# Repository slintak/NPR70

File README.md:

# NPR70 — New Packet Radio for 70 cm Band

A complete open-source hardware and firmware project for a modern IP packet
radio modem operating on the 70 cm amateur band (420–450 MHz).  Compatible with
the NPR [New Packet Radio](https://hackaday.io/project/164092-npr-new-packet-radio),
but with custom hardware and improvements for easier DIY assembly.

## What is NPR70?

**NPR70** is an open-source implementation of a New Packet Radio (NPR) modem — a
  protocol and hardware design for transmitting IP packets over UHF (70 cm)
  amateur radio, with the following goals:

- High throughput (typically 50–500 kbps gross rate)
- Reliable point-to-multipoint IP networking (TCP/IP, UDP, etc.)
- Fully open hardware and software
- Minimal latency and straightforward configuration

This project is **primarily for amateur radio operators** interested in building
and experimenting with modern digital data networks, Hamnet, telemetry, or
similar applications on the UHF band.

It is a fork/derivative of the
[original NPR project by F4HDK](https://hackaday.io/project/164092-npr-new-packet-radio),
but with new custom hardware, simplified design, and refactored/cleaned firmware.

## Who is this for?

- Licensed amateur radio operators interested in high-speed IP digital modes
- Hamnet and HSMM enthusiasts
- Anyone interested in open hardware wireless networking on UHF

## Hardware Overview

- **MCU**: STM32 microcontroller (STM32L432KCU, as in original)
- **RF Module**: NiceRF module for 70 cm UHF band  (based on SI4463)
- **Ethernet**: W5500 (SPI, 10/100 Mbps Ethernet controller)
- **Form Factor**: Two layer 69×100 mm PCB
- **Other**: 0402 SMD passives, SMA, Ethernet and USB-C connectors, etc.

The hardware is designed to be compact and affordable, with a focus on
DIY manufacturing and community development. All schematics and layout
files are in the [`pcb/`](pcb/) directory.

## Firmware Details

- Based on **MbedOS 5.6.6** (last version compatible with the original code)
- Derived from the [F4HDK NPR firmware]
  (https://github.com/f4hdk/NewPacketRadio), but refactored and cleaned up for
  different pinout
- Supports all main NPR features (TDMA master/slave, 2GFSK/4GFSK,
  point-to-multipoint IP bridging)
- Compatible with official NPR protocol and other compatible modems

## Key Features

| Feature        | Details                                                     |
|----------------|-------------------------------------------------------------|
| **Protocol**   | NPR (custom IP radio, NOT AX.25; true L3)                   |
| **Topology**   | Point-to-multipoint (master + up to 7 clients), TDMA        |
| **Modulation** | 2GFSK / 4GFSK, up to 500 kbps gross (see protocol docs)     |
| **RF Band**    | 70 cm amateur band (configurable, typically 430–440 MHz)    |
| **Network**    | Full IP stack, transparent bridging, works with DHCP, TCP/IP, UDP, etc. |
| **Range**      | Up to 300 km line-of-sight (with suitable antennas and power) |
| **Hardware**   | STM32 MCU, SI4463 radio, W5500 Ethernet, all open hardware  |
| **License**    | GPL v3.0 (same as original NPR project)                     |

## Repository Structure

- `pcb/` – KiCAD project directory (schematic and PCB layout).
- `src/` – Firmware source code, based on MbedOS (legacy version), derived and
  adapted from the original NPR project.

## Quick Start

1. **Hardware**: Manufacture or assemble the PCB found in `pcb/`. BOM and
   assembly notes are included.
2. **Firmware**:
    - For building the code by youself, you will need Debian based system and
      installed `gcc-arm-none-eabi`.
    - Build firmware by running `make` in the `src/` directory.
    - Firmware binary is in  the `src/BUILD/NPR70.hex` file
    - Flash firmware to the STM32 MCU using an SWD programmer
      `pyocd load -t stm32l432kc BUILD/NPR70.hex`
3. **Configuration**: Adjust radio parameters (frequency, bandwidth,
   master/client mode, IP addresses) as described in the
   [original NPR documentation](https://cdn.hackaday.io/files/1640927020512128/NPR70_introduction_EN_v3.6.pdf)
4. **Connect**: Plug in Ethernet and power, connect antenna, and start experimenting

Basic settings to check (more details in the original NPR documentation):

* `display config`: show current configuration
* `set <param> <value>`: store value to the given parameter
* `save`: saves current configuration into the EEPROM
* `radio on`/`radio off`: turn RF on or off
* `reboot`: reboot the FW

You have to set your callsign, frequency and modulation. Rest of the parameters
is up to you and your setup.

```
set callsign AB1CDE
set frequency 434.200
set modulation 22
```

## Documentation and References

- [Original NPR project by F4HDK](https://hackaday.io/project/164092-npr-new-packet-radio)
- [Official NPR documentation (PDFs, guides, protocol)](https://cdn.hackaday.io/files/1640927020512128/NPR70_introduction_EN_v3.6.pdf)
- [Project homepage and build log (in Czech)](https://uart.cz/2773/the-new-packet-radio/)

## License

This project is released under the **GPL v3.0 license**, same as the original
NPR project by F4HDK. See [LICENSE](LICENSE) for full details.

## Contributing

Contributions are welcome! You can:

- Submit hardware design improvements (new PCB revisions, bugfixes)
- Help with firmware optimization, porting to newer MbedOS versions, or adding
  features
- Share test results, deployment reports, and real-world feedback
- Translate documentation

For major changes, please open an issue first to discuss what you would like to
change.

If you have questions or suggestions, feel free to open an
[issue](https://github.com/slintak/NPR70/issues).

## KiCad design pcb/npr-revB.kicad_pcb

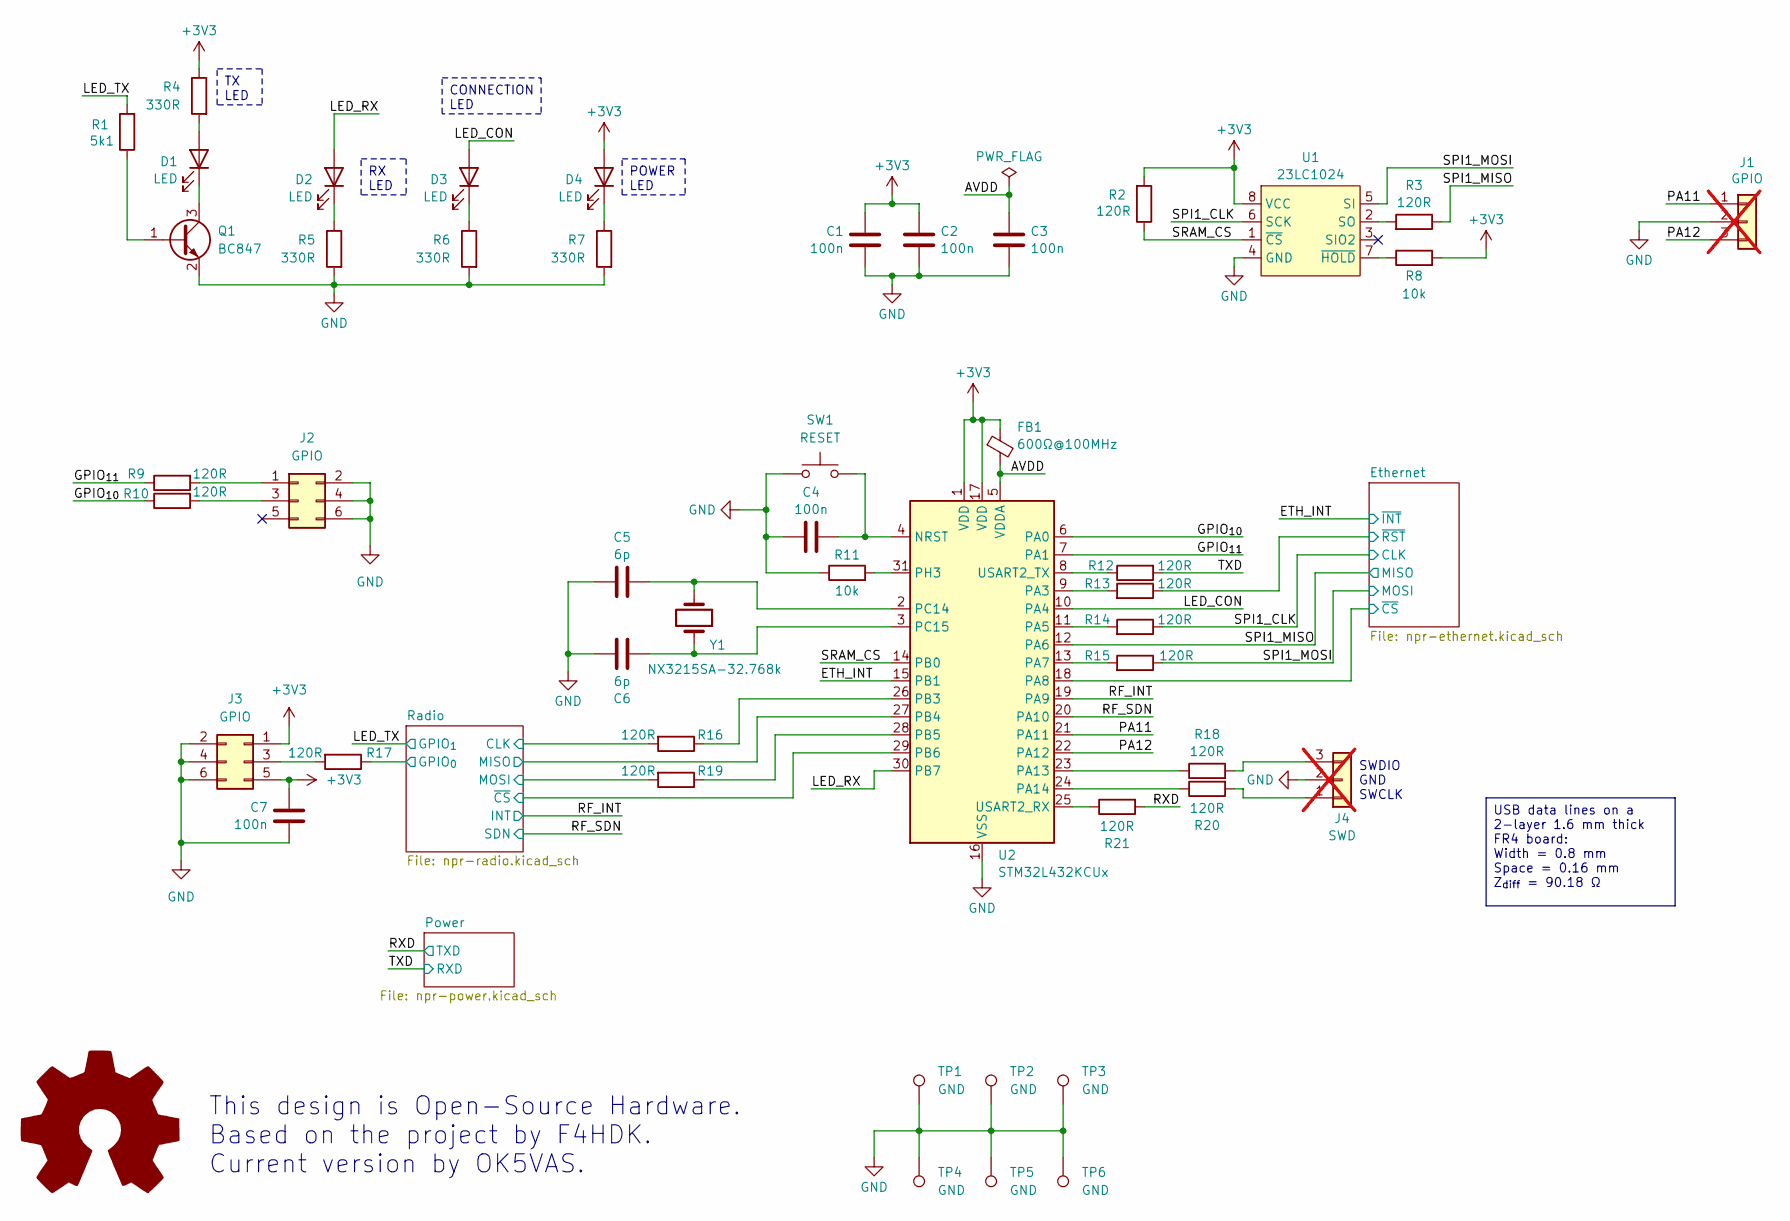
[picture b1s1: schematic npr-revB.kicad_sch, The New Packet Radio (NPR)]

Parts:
C1, C2, C3, C4, C7: 100n; C_0402_1005Metric; LCSC C1525
C5, C6: 6p; C_0402_1005Metric; LCSC C700515
D1, D2, D3, D4: LED; LED_0603_1608Metric; LCSC C2286
FB1: 600Ω@100MHz; L_0603_1608Metric; LCSC C19330
J1: GPIO; PinHeader_1x03_P2.54mm_Vertical; not fitted
J2, J3: GPIO; IDC-Header_2x03_P2.54mm_Horizontal; LCSC C34945
J4: SWD; PinHeader_1x03_P2.54mm_Vertical; not fitted
Q1: BC847; SOT-23; LCSC C57668
R1: 5k1; R_0402_1005Metric; LCSC C25905
R2, R3, R9, R10, R12, R13, R14, R15, R16, R17, R18, R19, R20, R21: 120R; R_0402_1005Metric; LCSC C25079
R4, R5, R6, R7: 330R; R_0402_1005Metric; LCSC C12246
R8, R11: 10k; R_0402_1005Metric; LCSC C25744
SW1: RESET; SW_SPST_CK_RS282G05A3; LCSC C483808
TP1, TP2, TP3, TP4, TP5, TP6: GND; TestPoint_Pad_D3.0mm
U1: 23LC1024; SOP-8_3.9x4.9mm_P1.27mm; LCSC C48388
U2: STM32L432KCUx; QFN-32-1EP_5x5mm_P0.5mm_EP3.45x3.45mm; LCSC C1337280
Y1: NX3215SA-32.768k; Crystal_SMD_3215-2Pin_3.2x1.5mm; LCSC C156244

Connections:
+3V3: C1.1, C2.1, C7.1, D4.2 (A), FB1.1, J3.1, J3.5, R2.2, R4.1, R8.2, U1.8 (VCC), U2.1 (VDD), U2.17 (VDD); also elsewhere on the board
/AVDD: C3.1, FB1.2, U2.5 (VDDA)
/ETH_INT: U2.15 (PB1); also elsewhere on the board
/Ethernet/~CS: U2.18 (PA8); also elsewhere on the board
/Ethernet/~RST: R13.1; also elsewhere on the board
/GPIO_{10}: R10.1, U2.6 (PA0)
/GPIO_{11}: R9.1, U2.7 (PA1)
/LED_CON: D3.2 (A), U2.10 (PA4)
/LED_RX: D2.2 (A), U2.30 (PB7)
/LED_TX: R1.2; also elsewhere on the board
/PA11: J1.1, U2.21 (PA11)
/PA12: J1.3, U2.22 (PA12)
/RF_INT: U2.19 (PA9); also elsewhere on the board
/RF_SDN: U2.20 (PA10); also elsewhere on the board
/RXD: R21.2; also elsewhere on the board
/Radio/CLK: R16.2; also elsewhere on the board
/Radio/GPIO_{0}: R17.1; also elsewhere on the board
/Radio/MISO: U2.27 (PB4); also elsewhere on the board
/Radio/MOSI: R19.2; also elsewhere on the board
/Radio/~CS: U2.29 (PB6); also elsewhere on the board
/SPI1_CLK: R14.1, U1.6 (SCK); also elsewhere on the board
/SPI1_MISO: R3.1, U2.12 (PA6); also elsewhere on the board
/SPI1_MOSI: R15.1, U1.5 (SI); also elsewhere on the board
/SRAM_CS: R2.1, U1.1 (~CS), U2.14 (PB0)
/TXD: R12.2; also elsewhere on the board
GND: C1.2, C2.2, C3.2, C4.1, C5.1, C6.1, C7.2, J1.2, J2.2, J2.4, J2.6, J3.2, J3.4, J3.6, J4.2, Q1.2 (E), R5.2, R6.2, R7.2, R11.1, SW1.1, TP1.1, TP2.1, TP3.1, TP4.1, TP5.1, TP6.1, U1.4 (GND), U2.16 (VSS), U2.32 (VSS), U2.33 (VSS); also elsewhere on the board
unnamed: D1.2 (A), R4.2
unnamed: D1.1 (K), Q1.3 (C)
unnamed: D2.1 (K), R5.1
unnamed: D3.1 (K), R6.1
unnamed: D4.1 (K), R7.1
unnamed: J2.1, R9.2
unnamed: J2.3, R10.2
unnamed: J3.3, R17.2
unnamed: J4.1, R20.2
unnamed: J4.3, R18.2
unnamed: Q1.1 (B), R1.1
unnamed: R3.2, U1.2 (SO)
unnamed: R8.1, U1.7 (~HOLD)
unnamed: C4.2, SW1.2, U2.4 (NRST)
unnamed: R12.1, U2.8 (USART2_TX)
unnamed: R13.2, U2.9 (PA3)
unnamed: R14.2, U2.11 (PA5)
unnamed: R15.2, U2.13 (PA7)
unnamed: R18.1, U2.23 (PA13)
unnamed: R20.1, U2.24 (PA14)
unnamed: R21.1, U2.25 (USART2_RX)
unnamed: R16.1, U2.26 (PB3)
unnamed: R19.1, U2.28 (PB5)
unnamed: C5.2, U2.2 (PC14), Y1.2
unnamed: C6.2, U2.3 (PC15), Y1.1
unnamed: R11.2, U2.31 (PH3)

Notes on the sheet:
This design is Open-Source Hardware. Based on the project by F4HDK. Current version by OK5VAS.
SWDIO GND SWCLK
RX LED
CONNECTION LED
TX LED
POWER LED
USB data lines on a 2-layer 1.6 mm thick FR4 board: Width = 0.8 mm Space = 0.16 mm Z_{diff} = 90.18 Ω

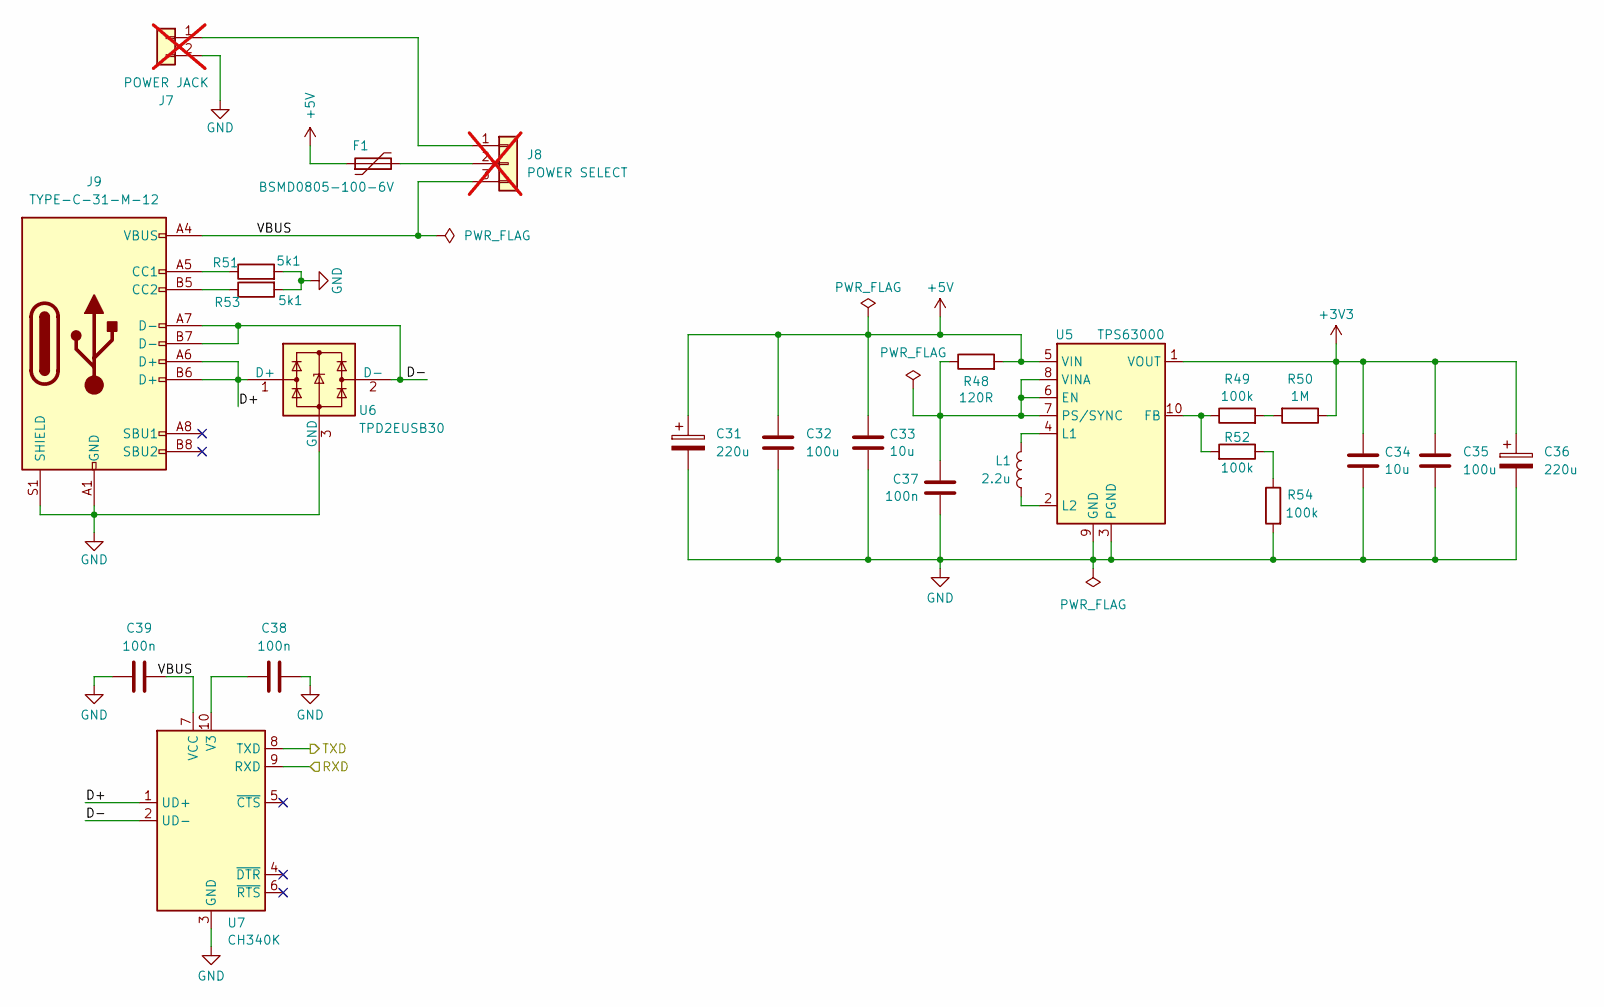
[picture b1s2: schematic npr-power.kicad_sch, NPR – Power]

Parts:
C31, C36: 220u; CP_Elec_6.3x5.4; LCSC C2833309
C32, C35: 100u; C_1206_3216Metric; LCSC C15008
C33, C34: 10u; C_0603_1608Metric; LCSC C19702
C37, C38, C39: 100n; C_0402_1005Metric; LCSC C1525
F1: BSMD0805-100-6V; Fuse_0805_2012Metric; LCSC C883112
J7: POWER JACK; PinHeader_1x02_P2.54mm_Vertical; not fitted
J8: POWER SELECT; PinHeader_1x03_P2.54mm_Vertical; not fitted
J9: TYPE-C-31-M-12; USB_C_Receptacle_HRO_TYPE-C-31-M-12; LCSC C165948
L1: 2.2u; L_Taiyo-Yuden_MD-3030; LCSC C5159665
R48: 120R; R_0402_1005Metric; LCSC C25079
R49, R52, R54: 100k; R_0402_1005Metric; LCSC C25741
R50: 1M; R_0402_1005Metric; LCSC C26083
R51, R53: 5k1; R_0402_1005Metric; LCSC C25905
U5: TPS63000; Texas_DRC0010J_ThermalVias; LCSC C24966
U6: TPD2EUSB30; Texas_DRT-3; LCSC C97502
U7: CH340K; SSOP-10-1EP_3.9x4.9mm_P1mm_EP2.1x3.3mm; LCSC C18208922

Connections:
+3V3: C34.1, C35.1, C36.1, R50.1, U5.1 (VOUT); also elsewhere on the board
+5V: C31.1, C32.1, C33.1, F1.1, R48.2, U5.5 (VIN); also elsewhere on the board
/Power/D+: J9.A6 (D+), J9.B6 (D+), U6.1 (D+), U7.1 (UD+)
/Power/D-: J9.A7 (D-), J9.B7 (D-), U6.2 (D-), U7.2 (UD-)
/Power/VBUS: C39.2, J8.3, J9.A4 (VBUS), J9.A9 (VBUS), J9.B4 (VBUS), J9.B9 (VBUS), U7.7 (VCC)
/RXD: U7.8 (TXD); also elsewhere on the board
/TXD: U7.9 (RXD); also elsewhere on the board
GND: C31.2, C32.2, C33.2, C34.2, C35.2, C36.2, C37.2, C38.2, C39.1, J7.2, J9.A1 (GND), J9.A12 (GND), J9.B1 (GND), J9.B12 (GND), J9.S1 (SHIELD), R51.2, R53.2, R54.2, U5.3 (PGND), U5.9 (GND), U5.11 (PGND), U6.3 (GND), U7.3 (GND), U7.11 (GND); also elsewhere on the board
unnamed: J7.1, J8.1
unnamed: F1.2, J8.2
unnamed: J9.A5 (CC1), R51.1
unnamed: J9.B5 (CC2), R53.1
unnamed: R49.2, R50.2
unnamed: R52.1, R54.1
unnamed: C37.1, R48.1, U5.6 (EN), U5.7 (PS/SYNC), U5.8 (VINA)
unnamed: R49.1, R52.2, U5.10 (FB)
unnamed: L1.2, U5.4 (L1)
unnamed: L1.1, U5.2 (L2)
unnamed: C38.1, U7.10 (V3)

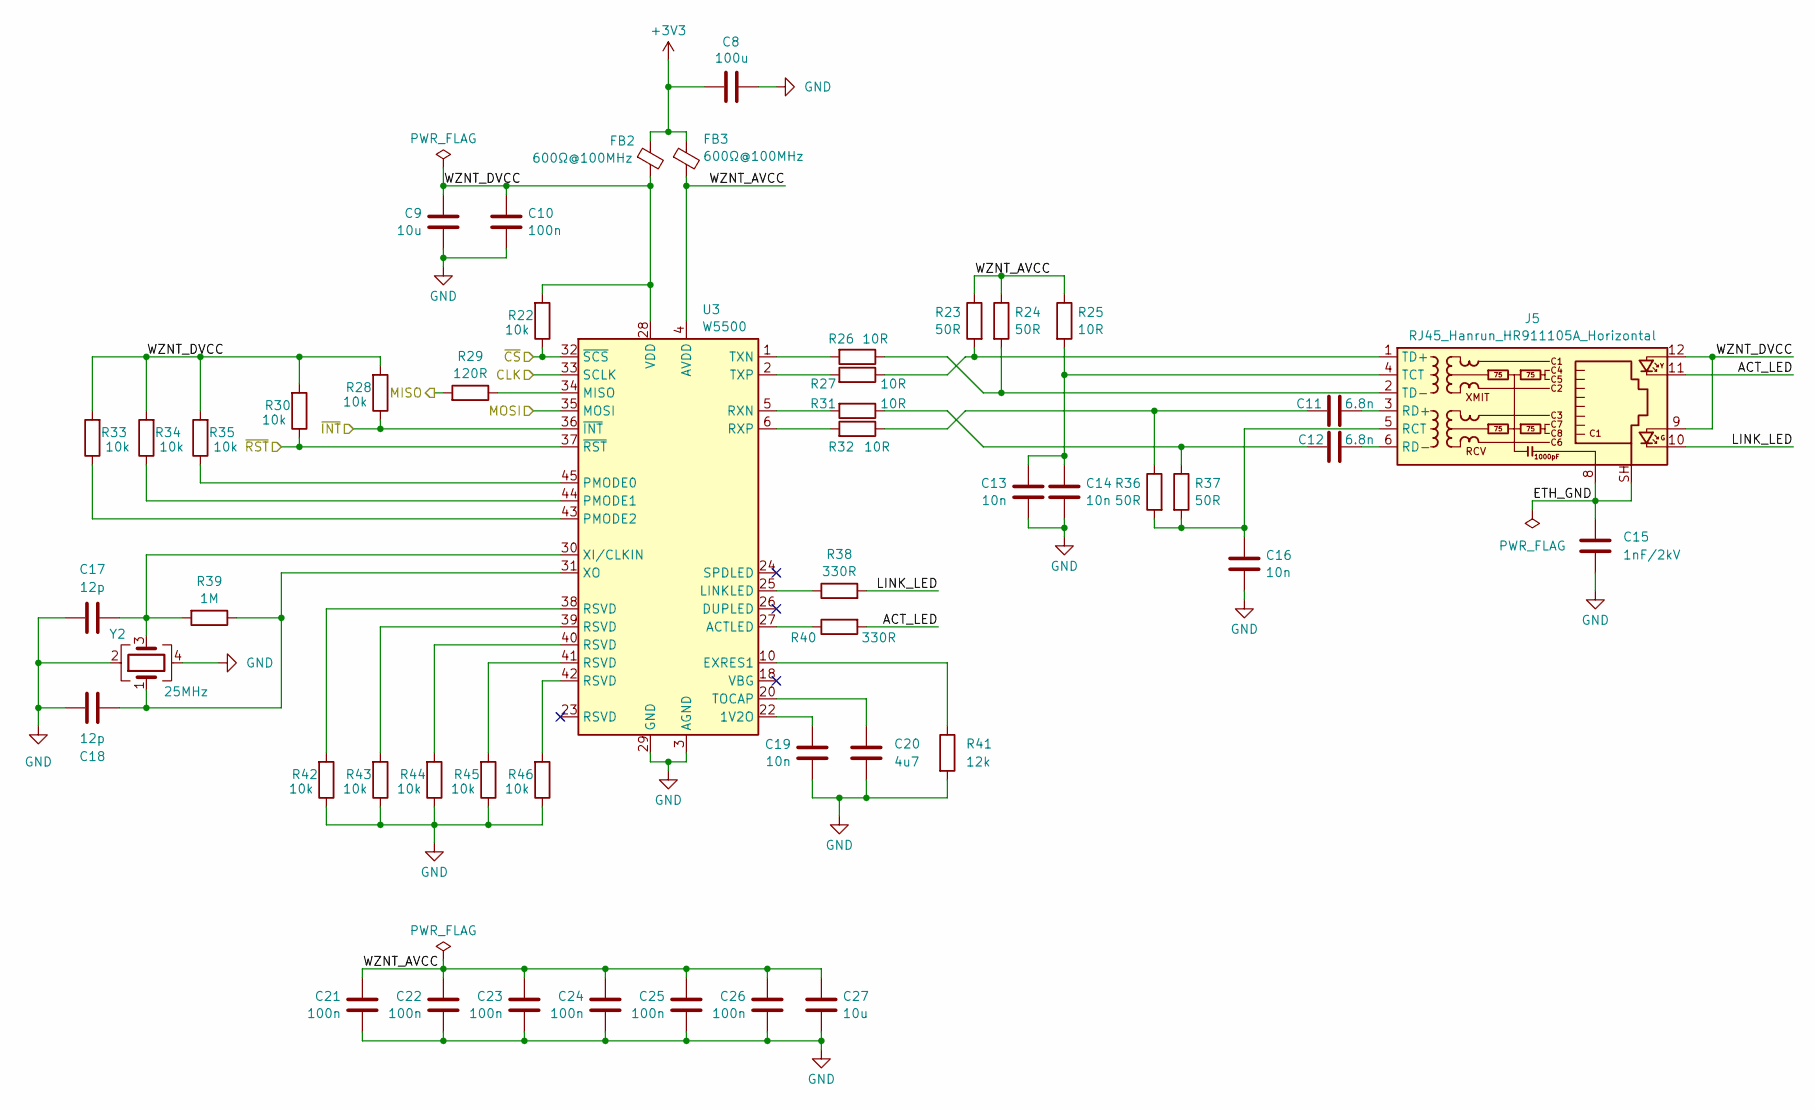
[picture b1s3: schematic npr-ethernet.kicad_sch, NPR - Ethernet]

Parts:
C8: 100u; C_1206_3216Metric; LCSC C15008
C9, C27: 10u; C_0402_1005Metric; LCSC C15525
C10, C21, C22, C23, C24, C25, C26: 100n; C_0402_1005Metric; LCSC C1525
C11, C12: 6.8n; C_0402_1005Metric; LCSC C93654
C13, C14, C16, C19: 10n; C_0402_1005Metric; LCSC C318577
C15: 1nF/2kV; C_1206_3216Metric; LCSC C23631
C17, C18: 12p; C_0402_1005Metric; LCSC C106201
C20: 4u7; C_0402_1005Metric; LCSC C23733
FB2, FB3: 600Ω@100MHz; L_0603_1608Metric; LCSC C19330
J5: RJ45_Hanrun_HR911105A_Horizontal; LCSC C12074
R22, R28, R30, R33, R34, R35, R42, R43, R44, R45, R46: 10k; R_0402_1005Metric; LCSC C25744
R23, R24, R36, R37: 50R; R_0402_1005Metric; LCSC C227387
R25, R26, R27, R31, R32: 10R; R_0402_1005Metric; LCSC C25139
R29: 120R; R_0402_1005Metric; LCSC C25079
R38, R40: 330R; R_0402_1005Metric; LCSC C12246
R39: 1M; R_0402_1005Metric; LCSC C26083
R41: 12k; R_0402_1005Metric; LCSC C25752
U3: W5500; LQFP-48_7x7mm_P0.5mm; LCSC C32843
Y2: 25MHz; Crystal_SMD_3225-4Pin_3.2x2.5mm; LCSC C9006

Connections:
+3V3: C8.1, FB2.1, FB3.1; also elsewhere on the board
/ETH_INT: R28.1, U3.36 (~INT); also elsewhere on the board
/Ethernet/ACT_LED: J5.11, R40.2
/Ethernet/ETH_GND: C15.1, J5.8, J5.SH
/Ethernet/LINK_LED: J5.10, R38.2
/Ethernet/WZNT_AVCC: C21.1, C22.1, C23.1, C24.1, C25.1, C26.1, C27.1, FB3.2, R23.1, R24.1, R25.1, U3.4 (AVDD), U3.8 (AVDD), U3.11 (AVDD), U3.15 (AVDD), U3.17 (AVDD), U3.21 (AVDD)
/Ethernet/WZNT_DVCC: C9.1, C10.1, FB2.2, J5.9, J5.12, R22.2, R28.2, R30.2, R33.2, R34.2, R35.2, U3.28 (VDD)
/Ethernet/~CS: R22.1, U3.32 (~SCS); also elsewhere on the board
/Ethernet/~RST: R30.1, U3.37 (~RST); also elsewhere on the board
/SPI1_CLK: U3.33 (SCLK); also elsewhere on the board
/SPI1_MISO: R29.2; also elsewhere on the board
/SPI1_MOSI: U3.35 (MOSI); also elsewhere on the board
GND: C8.2, C9.2, C10.2, C13.2, C14.2, C15.2, C16.2, C17.2, C18.2, C19.2, C20.2, C21.2, C22.2, C23.2, C24.2, C25.2, C26.2, C27.2, R41.2, R42.1, R43.1, R44.1, R45.1, R46.1, U3.3 (AGND), U3.9 (AGND), U3.14 (AGND), U3.16 (AGND), U3.19 (AGND), U3.29 (GND), U3.48 (AGND), Y2.2, Y2.4; also elsewhere on the board
unnamed: C11.2, R32.1, R36.1
unnamed: C12.2, R31.1, R37.1
unnamed: C16.1, J5.5 (RCT), R36.2, R37.2
unnamed: C11.1, J5.3 (RD+)
unnamed: C12.1, J5.6 (RD-)
unnamed: C13.1, C14.1, J5.4 (TCT), R25.2
unnamed: J5.1 (TD+), R23.2, R27.1
unnamed: J5.2 (TD-), R24.2, R26.1
unnamed: R42.2, U3.38 (RSVD)
unnamed: R43.2, U3.39 (RSVD)
unnamed: R44.2, U3.40 (RSVD)
unnamed: R45.2, U3.41 (RSVD)
unnamed: R46.2, U3.42 (RSVD)
unnamed: C19.1, U3.22 (1V2O)
unnamed: R40.1, U3.27 (ACTLED)
unnamed: R41.1, U3.10 (EXRES1)
unnamed: R38.1, U3.25 (LINKLED)
unnamed: R29.1, U3.34 (MISO)
unnamed: R35.1, U3.45 (PMODE0)
unnamed: R34.1, U3.44 (PMODE1)
unnamed: R33.1, U3.43 (PMODE2)
unnamed: R31.2, U3.5 (RXN)
unnamed: R32.2, U3.6 (RXP)
unnamed: C20.1, U3.20 (TOCAP)
unnamed: R26.2, U3.1 (TXN)
unnamed: R27.2, U3.2 (TXP)
unnamed: C17.1, R39.2, U3.30 (XI/CLKIN), Y2.3
unnamed: C18.1, R39.1, U3.31 (XO), Y2.1

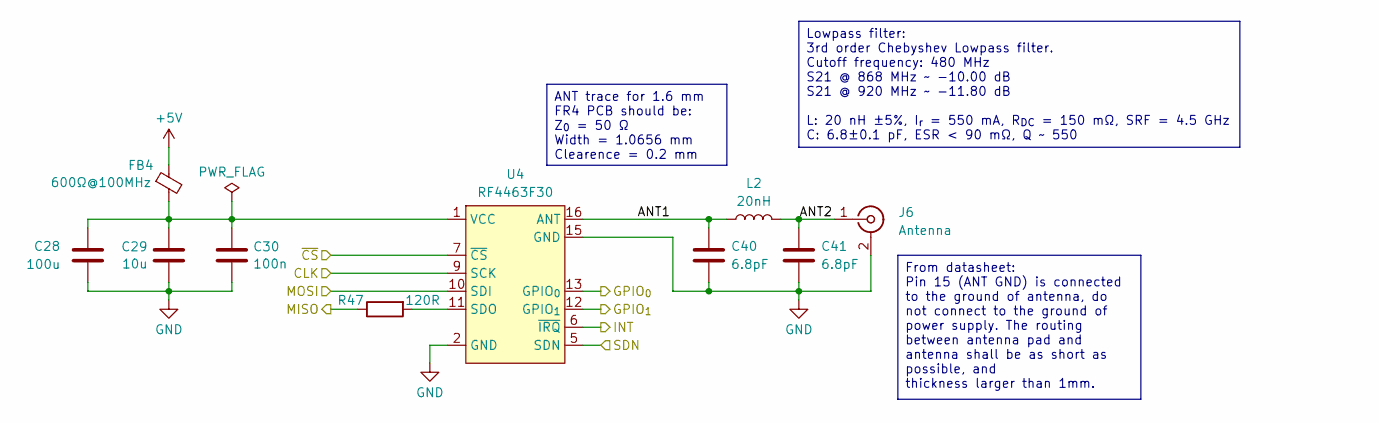
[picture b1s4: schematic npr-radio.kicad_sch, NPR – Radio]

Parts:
C28: 100u; C_1206_3216Metric; LCSC C15008
C29: 10u; C_0402_1005Metric; LCSC C15525
C30: 100n; C_0402_1005Metric; LCSC C1525
C40, C41: 6.8pF; C_0402_1005Metric; LCSC C88896
FB4: 600Ω@100MHz; L_0603_1608Metric; LCSC C19330
J6: Antenna; SMA_Amphenol_901-143_Horizontal; LCSC C411575
L2: 20nH; L_0603_1608Metric; LCSC C17702828
R47: 120R; R_0402_1005Metric; LCSC C25079
U4: RF4463F30; LCSC C5356658

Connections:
+5V: FB4.1; also elsewhere on the board
/LED_TX: U4.12 (GPIO_{1}); also elsewhere on the board
/RF_INT: U4.6 (~IRQ); also elsewhere on the board
/RF_SDN: U4.5 (SDN); also elsewhere on the board
/Radio/ANT1: C40.1, L2.1, U4.16 (ANT)
/Radio/ANT2: C41.1, J6.1 (In), L2.2
/Radio/CLK: U4.9 (SCK); also elsewhere on the board
/Radio/GPIO_{0}: U4.13 (GPIO_{0}); also elsewhere on the board
/Radio/MISO: R47.1; also elsewhere on the board
/Radio/MOSI: U4.10 (SDI); also elsewhere on the board
/Radio/~CS: U4.7 (~CS); also elsewhere on the board
GND: C28.2, C29.2, C30.2, C40.2, C41.2, J6.2 (Ext), U4.2 (GND), U4.8 (GND), U4.15 (GND); also elsewhere on the board
unnamed: R47.2, U4.11 (SDO)
unnamed: C28.1, C29.1, C30.1, FB4.2, U4.1 (VCC)

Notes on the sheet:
Lowpass filter: 3rd order Chebyshev Lowpass filter. Cutoff frequency: 480 MHz S21 @ 868 MHz ~ -10.00 dB S21 @ 920 MHz ~ -11.80 dB L: 20 nH ±5%, I_{r} = 550 mA, R_{DC} = 150 mΩ, SRF = 4.5 GHz C: 6.8±0.1 pF, ESR < 90 mΩ, Q ~ 550
From datasheet: Pin 15 (ANT GND) is connected to the ground of antenna, do not connect to the ground of power supply. The routing between antenna pad and antenna shall be as short as possible, and thickness larger than 1mm.
ANT trace for 1.6 mm FR4 PCB should be: Z_{0} = 50 Ω Width = 1.0656 mm Clearence = 0.2 mm

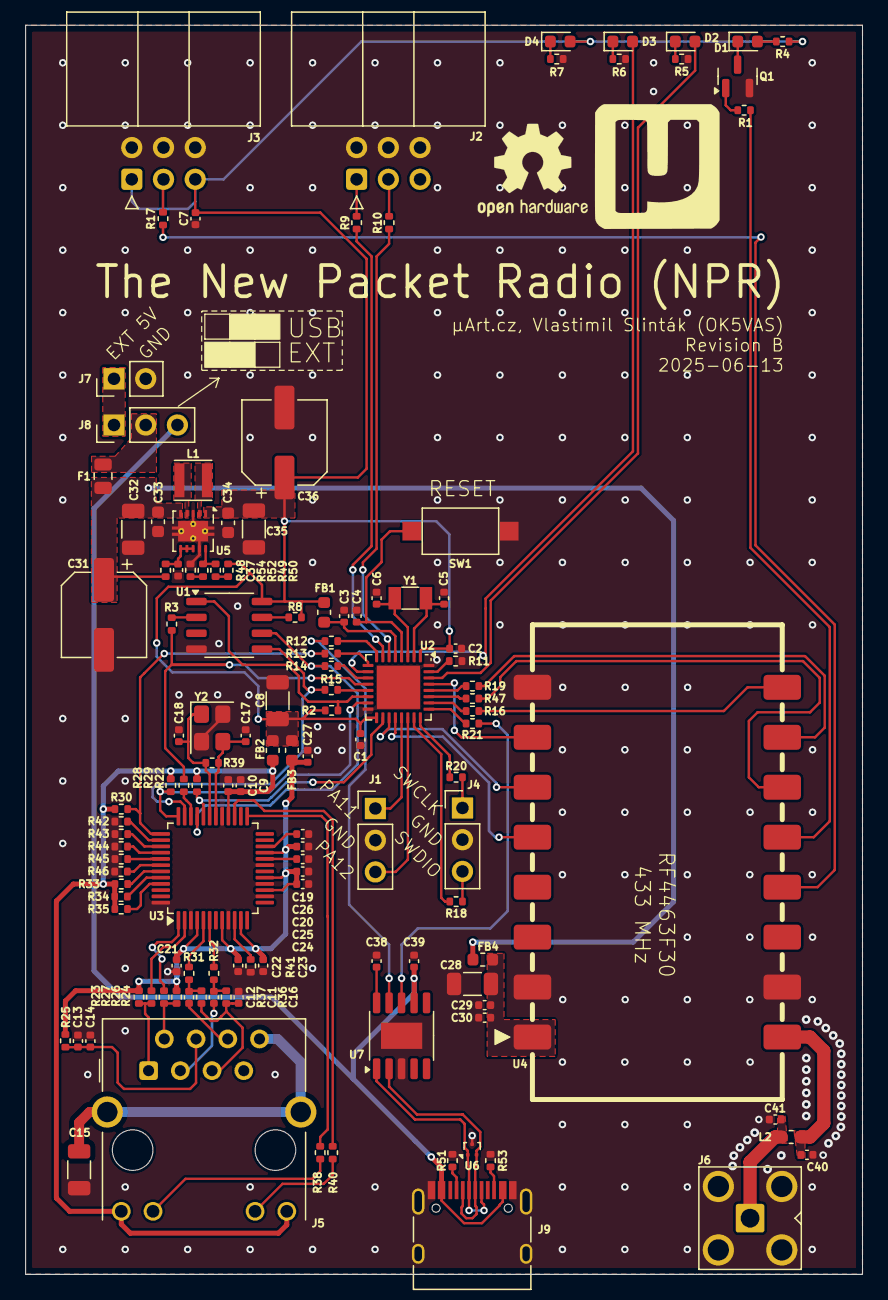
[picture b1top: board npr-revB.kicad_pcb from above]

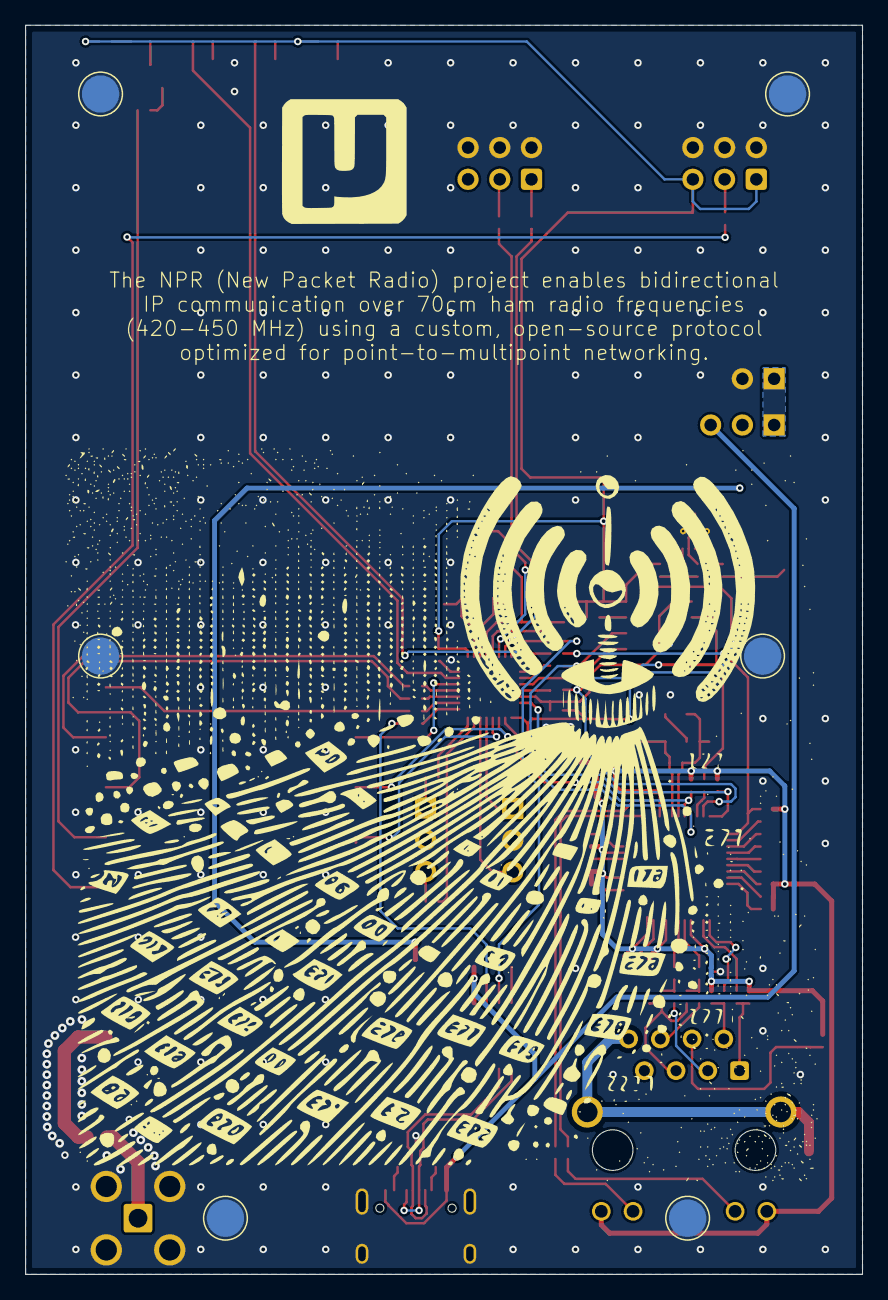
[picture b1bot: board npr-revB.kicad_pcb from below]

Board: 2 copper layers, 67.0 x 100.0 mm, 132 parts (6 on the bottom side), 104 nets.

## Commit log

2025-03-11 Initial commit with the original FW
    This FW for the New Packet Radio project was taken from the Hackaday
    project https://hackaday.io/project/164092-npr-new-packet-radio
    The source code is original without any modifications, ver. 2020_06_29.
2025-03-11 Ignore `build` directory
2025-03-11 Removed mbed-os files, we will use the project as submodule
2025-03-11 Use Mbed-OS 5.6.6 as a submodule
    This version was most probably the original Mbed-OS for this project.
2025-03-15 Fixed Makefile, use GNU++11 C++ standard
2025-03-15 Refactor SPI extension: use inheritance instead of modifying MbedOS files
2025-03-15 Fixed most of the compilers warnings, more refactoring needed
2025-03-15 Updated pinout for the new PCB version
2025-03-29 Use standard baudrate of 115200
2025-03-30 Set version to `2025_03_29`
2025-03-30 Set LICENSE to GPL3.0
    This is license of the original project from F4HDK, so we have to use the same.
2025-07-09 Use TRNG for random numbers instead of analog input pin.
2025-07-09 Changed line endings from DOS to Unix format
2025-07-09 Changed code formatting from tabs to spaces
2025-08-07 Moved source code to the `src/` subdirectory
2025-08-07 Added KiCAD project for the NPR revision B PCB
2025-08-07 Added readme file
2025-08-25 [WIP] Added Github Actions preset page
2025-08-25 Added Github Actions preset page
2025-08-26 User pandoc instead of py-markdown
2025-08-26 Fixed readme formatting
2025-08-26 Added FW build to the GH Action workflow
2025-08-26 Added firmware to the web
2025-12-31 Add `build/` to the gitignore
2025-12-31 README clarification
